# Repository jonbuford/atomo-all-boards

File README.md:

# atomo-all_boards
This is a collection of PCB designs for microcontroller development boards created for the Atomo line. We are releasing these files and designs to the world prior to our first production run. Any feedback on them is appreciated. 

Some basics:
1. We are releasing the raw design files and not the production silk screen with our commercial logo for Atomo. (We reserve the copyright on the Atomo brand.)
2. Yes, the refdes locations are on the parts for the most part. Earlier versions of the design attempted to keep all of the refdes markers in locations that could be used for silkscreen printing, but this required some very convoluted manual indications of what matches what. The density on these boards is just too high to have a clean 1:1 refdes printing on the boards. For the production silkscreens, we will be creating markings that is only for typical end use features and for major components or functional areas.
3. The 10-pin JTAG headers have been moved to the 26-pin/40-pin headers to reduce cost and to make all boards programmable using a Raspberry Pi or similar. 
4. Updated the 26-pin and 40-pin headers so that the pins are the same configuration for the first 26 pins. The 40-pin header is compatible with the ethernet adapter. 

So, this is the current state of the finished design files. To be added are the backplane and module files. The intent now is to try to move this into a more open development project to keep things growing. If you are interested in contributing, please contact the project.

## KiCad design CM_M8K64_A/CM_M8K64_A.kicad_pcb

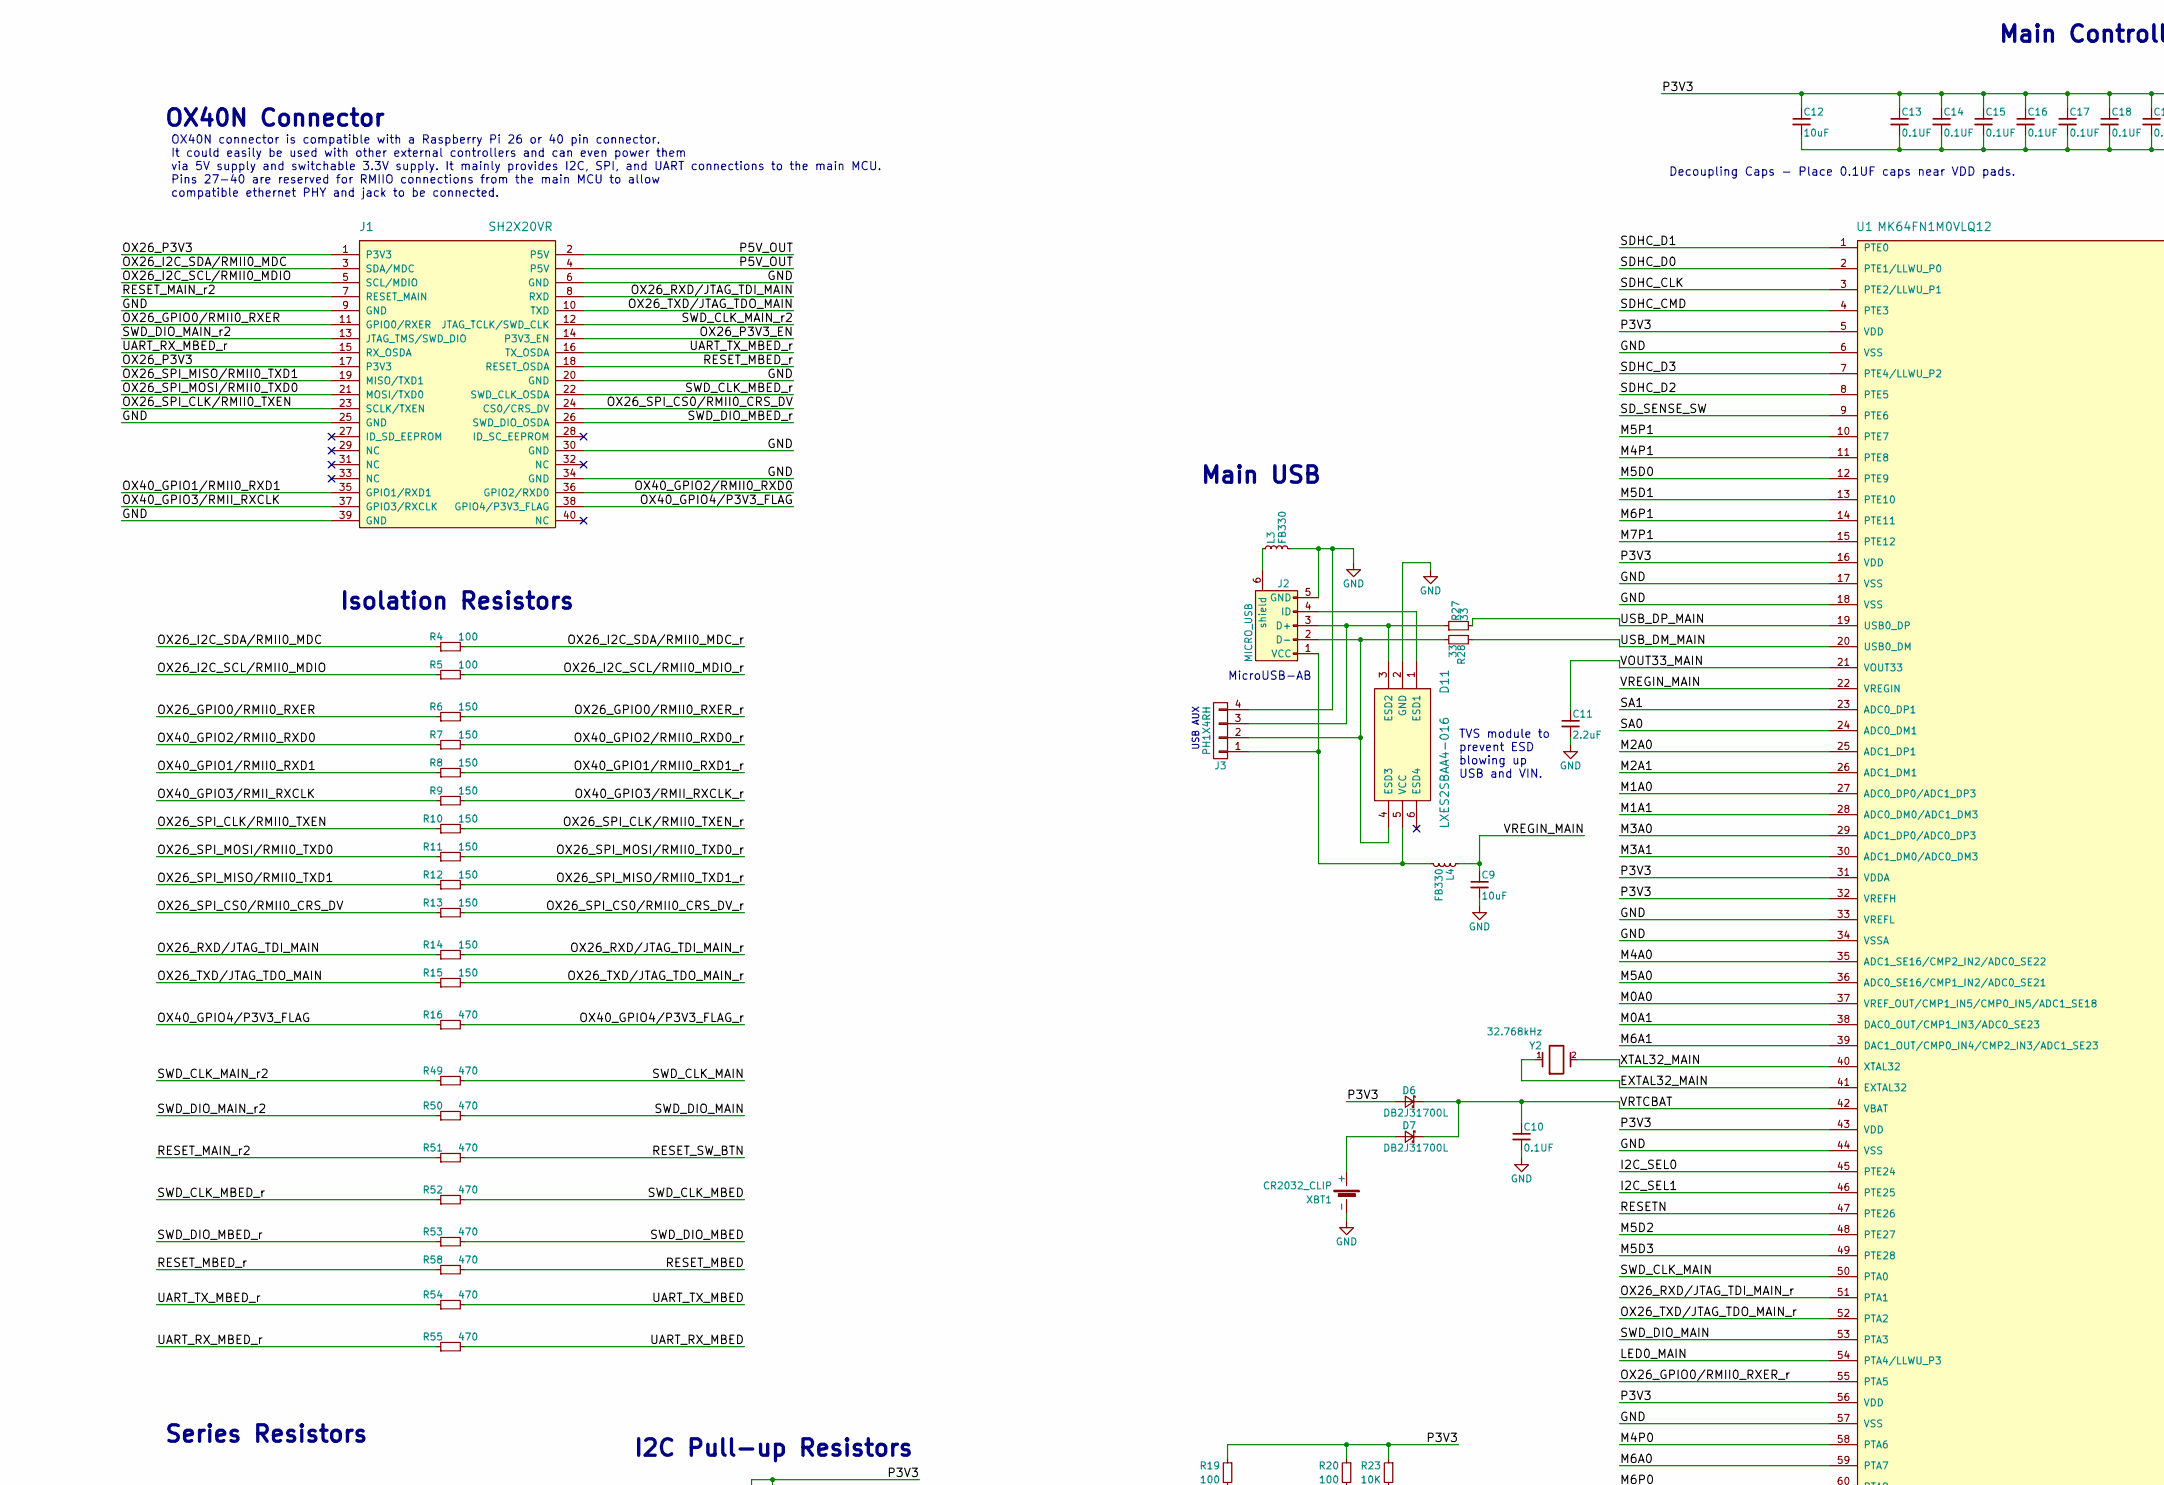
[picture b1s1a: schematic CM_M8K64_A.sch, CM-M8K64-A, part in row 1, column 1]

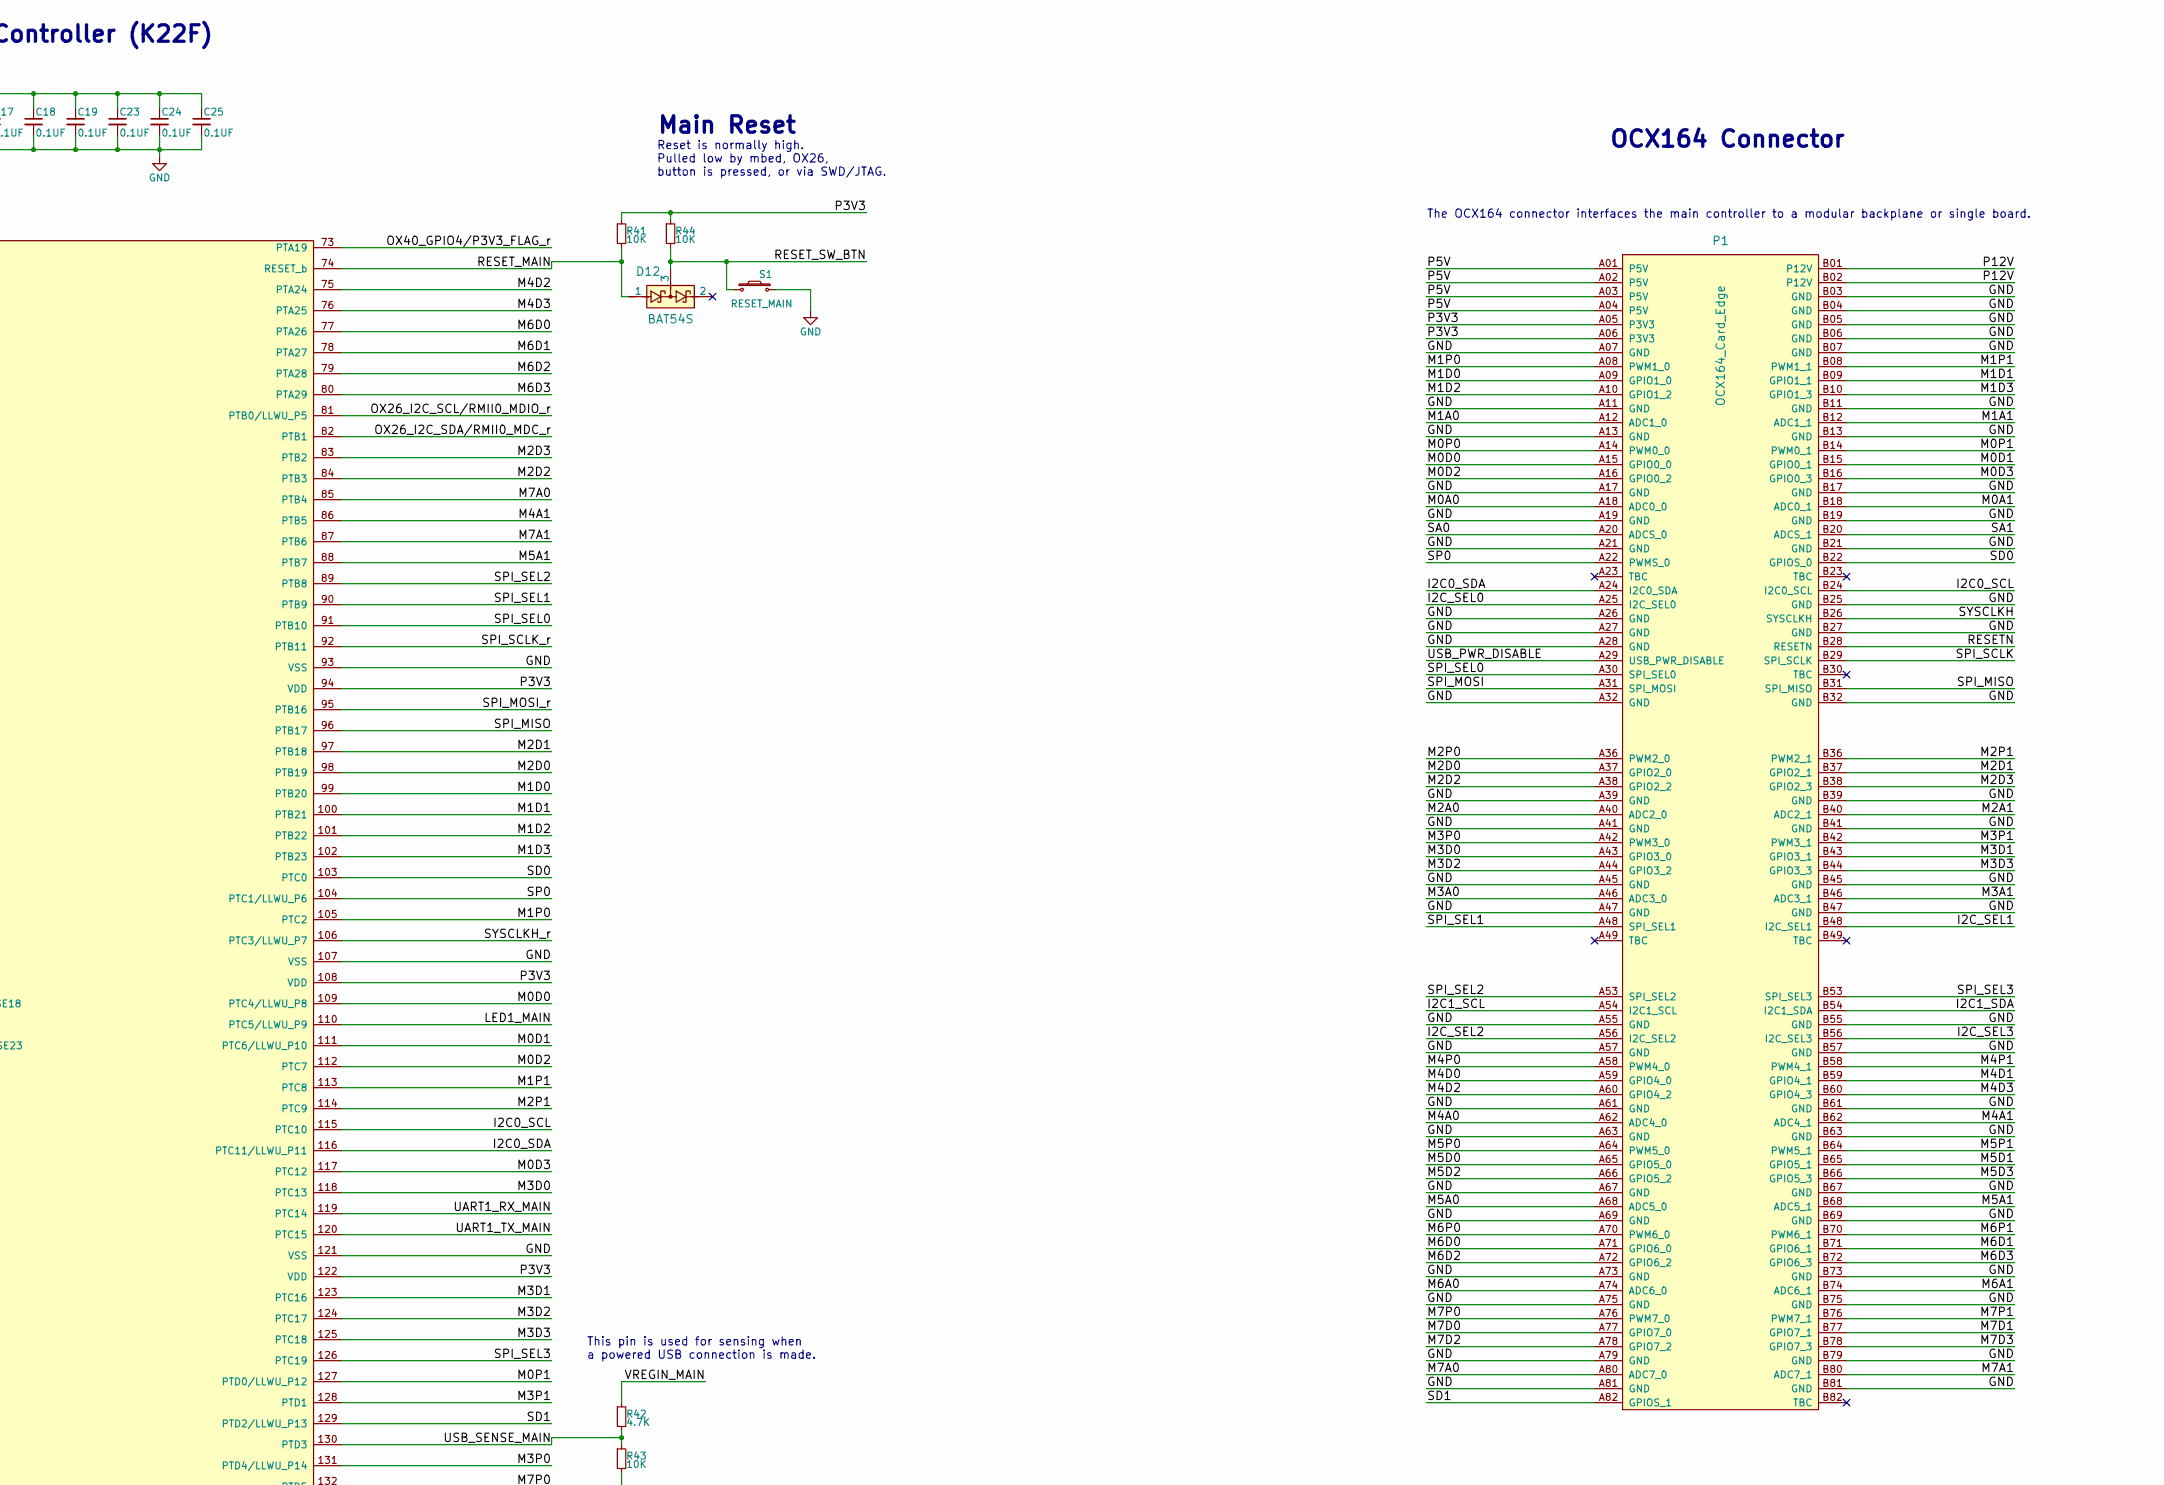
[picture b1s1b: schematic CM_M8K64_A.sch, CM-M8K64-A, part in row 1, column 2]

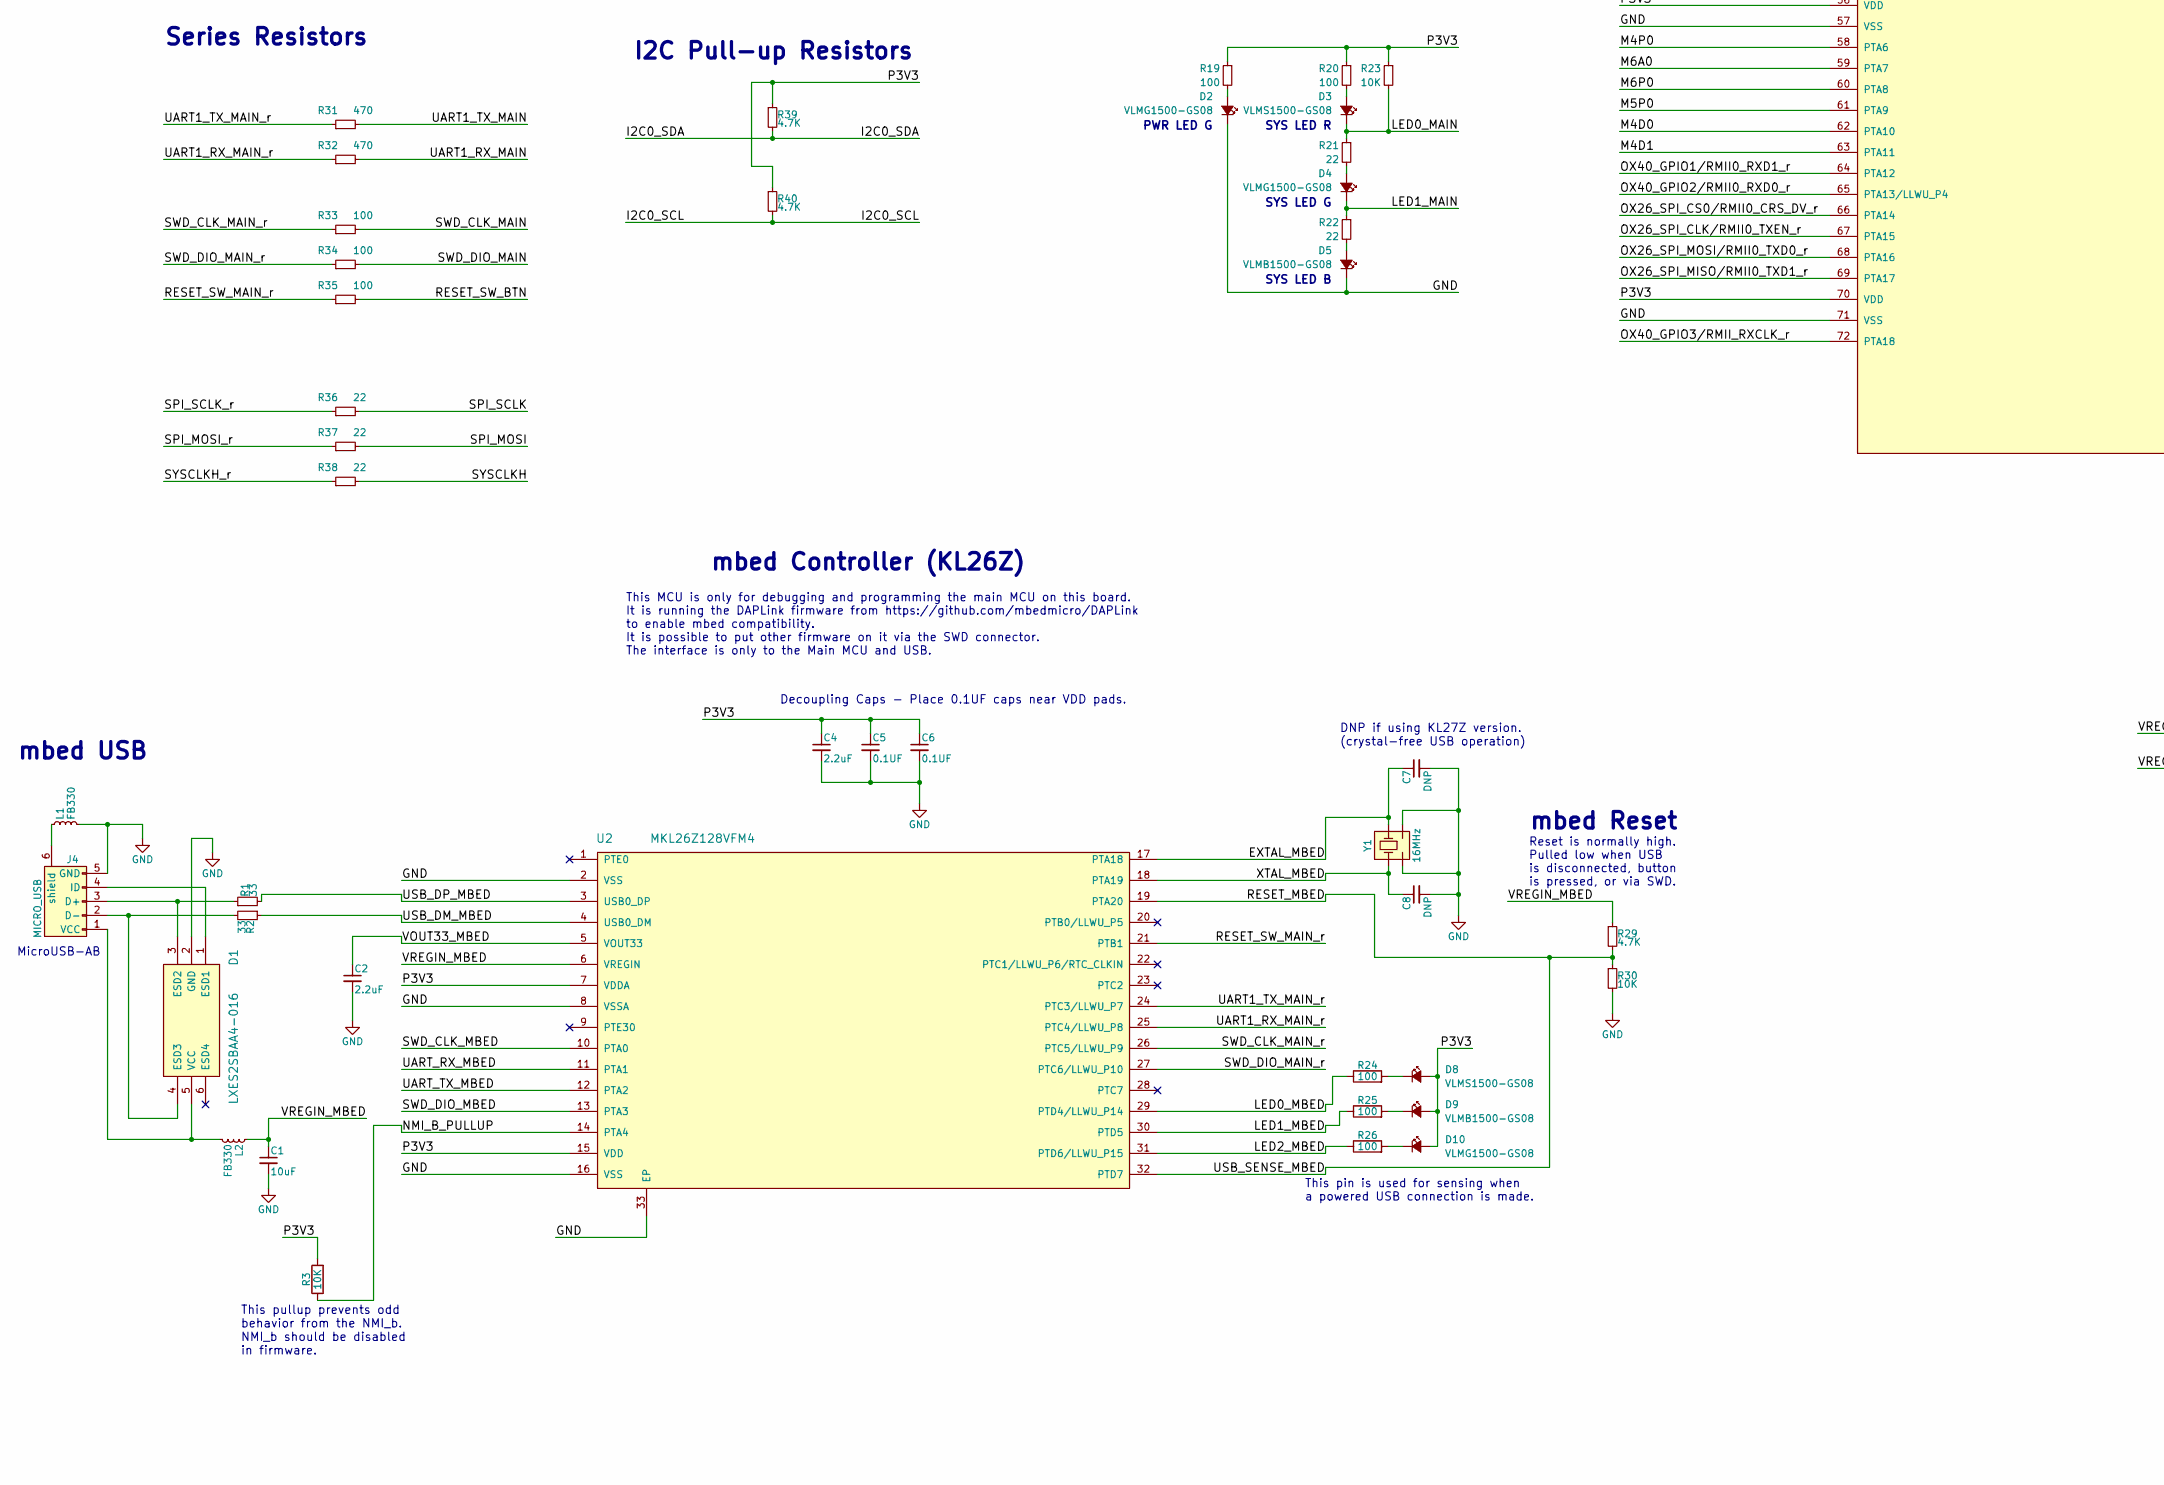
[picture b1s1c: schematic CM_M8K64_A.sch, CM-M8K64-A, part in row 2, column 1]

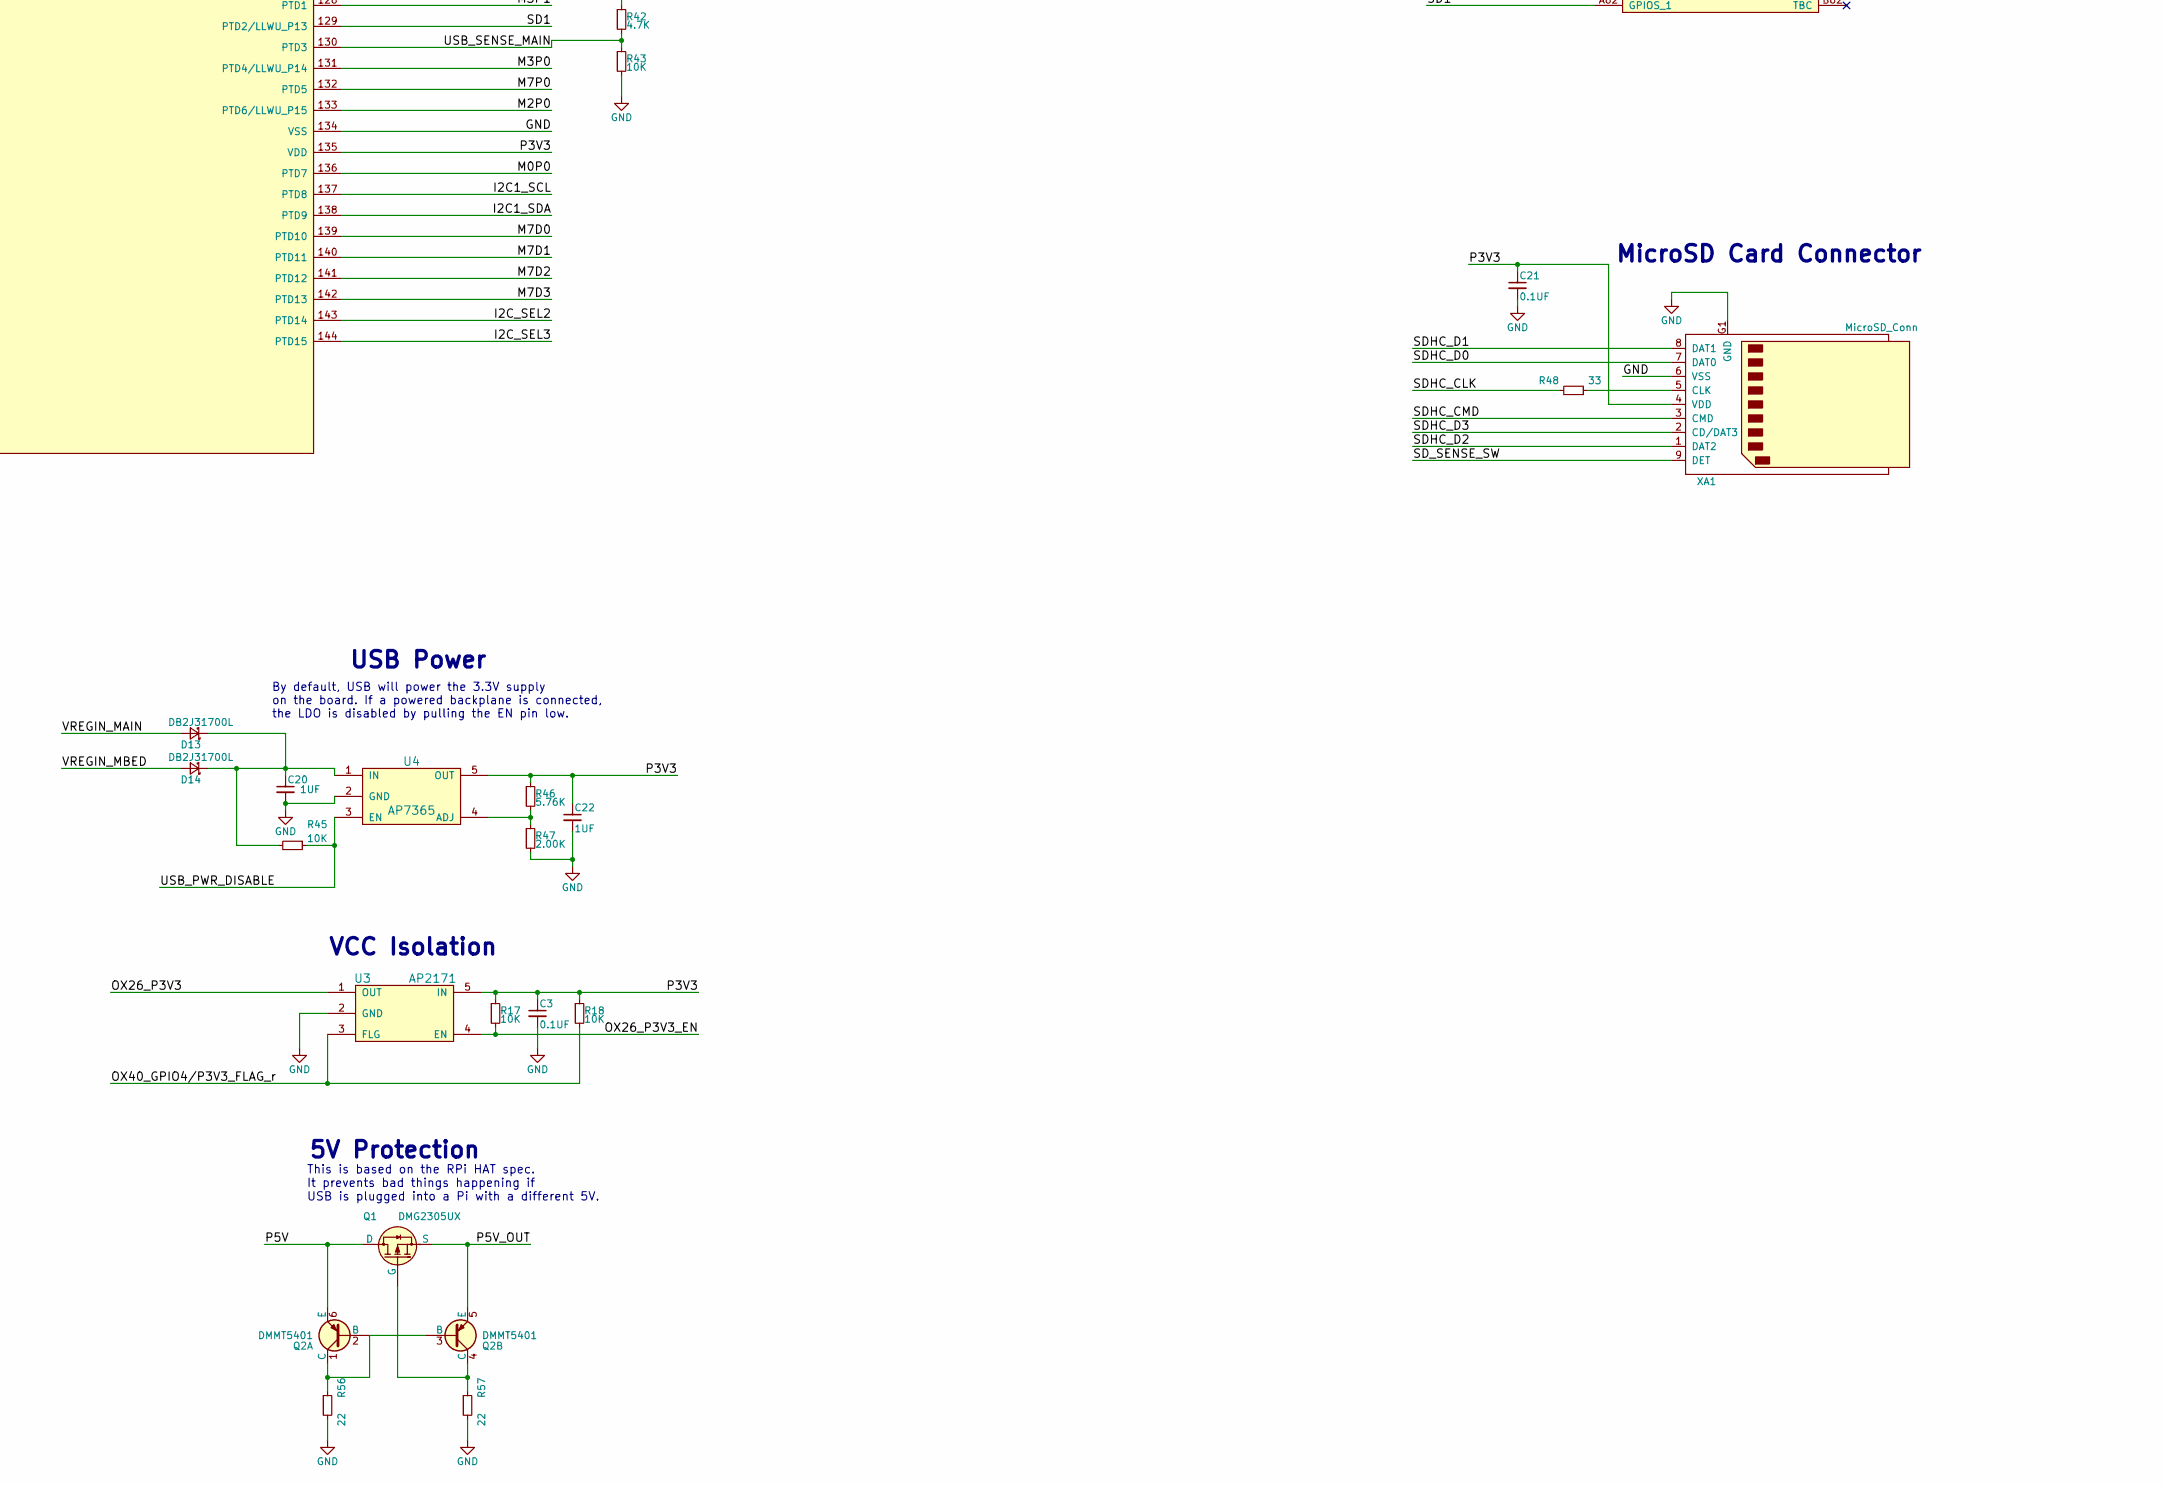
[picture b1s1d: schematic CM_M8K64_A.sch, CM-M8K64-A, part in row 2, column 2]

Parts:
C1, C9, C12: 10uF; C_0603; MPN GRM188R60J106KE47D
C2, C4, C11: 2.2uF; C_0402; MPN GRM155R60J225KE95D
C3, C5, C6, C10, C13, C14, C15, C16, C17, C18, C19, C21, C23, C24, C25: 0.1UF; C_0402; MPN GRM155R71H104ME14D
C7, C8: DNP; C_0402; MPN DNP
C20, C22: 1UF; C_0402; MPN GRM155R60J105KE19D
D1, D11: LXES2SBAA4-016; SOT-23-6; MPN LXES2SBAA4-016
D2, D4, D10: VLMG1500-GS08; LED_0402; MPN VLMG1500-GS08
D3, D8: VLMS1500-GS08; LED_0402; MPN VLMS1500-GS08
D5, D9: VLMB1500-GS08; LED_0402; MPN VLMB1500-GS08
D6, D7, D13, D14: DB2J31700L; SC-90A; MPN DB2J31700L
D12: BAT54S; SOT-23; MPN BAT54S,215
J1: SH2X20VR; OX40_W_PI_HOLE; MPN PPPC202LFBN-RC
J2, J4: MICRO_USB; Micro_USB_Molex_105017-0001; MPN 1050170001
J3: PH1X4RH; Pin_Header_Angled_1x04; MPN DNP
L1, L3: FB330; R_0603; MPN MPZ1608S331ATA00
L2, L4: FB330; R_0805; MPN MPZ2012S331AT000
P1: OCX164_Card_Edge; MPN DNP
Q1: DMG2305UX; SOT-23; MPN DMG2305UX-13
Q2: DMMT5401; SOT-23-6; MPN DMMT5401-7-F
R1, R2, R27, R28, R48: 33; R_0402; MPN RC0402JR-0733RL
R3, R17, R18, R23, R30, R41, R43, R44, R45: 10K; R_0402; MPN RC0402JR-0710KL
R4, R5, R19, R20, R24, R25, R26, R33, R34, R35: 100; R_0402; MPN RC0402JR-07100RL
R6, R7, R8, R9, R10, R11, R12, R13, R14, R15: 150; R_0402; MPN RC0402JR-07150RL
R16, R31, R32, R49, R50, R51, R52, R53, R54, R55, R58: 470; R_0402; MPN RC0402JR-07470RL
R21, R22, R36, R37, R38, R56, R57: 22; R_0402; MPN RC0402JR-0722RL
R29, R39, R40, R42: 4.7K; R_0402; MPN RC0402JR-074K7L
R46: 5.76K; R_0603; Tolerance 1%; MPN RC0603FR-075K76L
R47: 2.00K; R_0603; Tolerance 1%; MPN RC0603FR-072KL
S1: RESET_MAIN; Switch_TS-1101F_SZ_BEST; MPN TS-1101F
U1: MK64FN1M0VLQ12; LQFP-144_20x20mm_Pitch0.5mm; MPN MK64FN1M0VLQ12
U2: MKL26Z128VFM4; QFN32_w_TP_FS; MPN MKL26Z128VFM4
U3: AP2171; SOT-23-5; MPN AP2171WG-7
U4: AP7365; SOT-23-5; MPN AP7365-WG-7
XA1: MicroSD_Conn; 1051620101; MPN 1051620101
XBT1: CR2032_CLIP; KEYSTONE_3034; MPN 3034TR
Y1: 16MHz; XTAL3_2X2_5; MPN FA-238 16.0000MB-K3
Y2: 32.768kHz; XTAL_CYL_CAN_SMT; MPN G33270007

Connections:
/EXTAL32_MAIN: U1.41 (EXTAL32), Y2.1
/EXTAL_MBED: C7.1, U2.17 (PTA18), Y1.1
/I2C0_SCL: P1.B24 (I2C0_SCL), R40.2, U1.115 (PTC10)
/I2C0_SDA: P1.A24 (I2C0_SDA), R39.2, U1.116 (PTC11/LLWU_P11)
/I2C1_SCL: P1.A54 (I2C1_SCL), U1.137 (PTD8)
/I2C1_SDA: P1.B54 (I2C1_SDA), U1.138 (PTD9)
/I2C_SEL0: P1.A25 (I2C_SEL0), U1.45 (PTE24)
/I2C_SEL1: P1.B48 (I2C_SEL1), U1.46 (PTE25)
/I2C_SEL2: P1.A56 (I2C_SEL2), U1.143 (PTD14)
/I2C_SEL3: P1.B56 (I2C_SEL3), U1.144 (PTD15)
/LED0_MAIN: D3.1 (K), R21.1, R23.2, U1.54 (PTA4/LLWU_P3)
/LED0_MBED: R24.1, U2.29 (PTD4/LLWU_P14)
/LED1_MAIN: D4.1 (K), R22.1, U1.110 (PTC5/LLWU_P9)
/LED1_MBED: R25.1, U2.30 (PTD5)
/LED2_MBED: R26.1, U2.31 (PTD6/LLWU_P15)
/M0A0: P1.A18 (ADC0_0), U1.37 (VREF_OUT/CMP1_IN5/CMP0_IN5/ADC1_SE18)
/M0A1: P1.B18 (ADC0_1), U1.38 (DAC0_OUT/CMP1_IN3/ADC0_SE23)
/M0D0: P1.A15 (GPIO0_0), U1.109 (PTC4/LLWU_P8)
/M0D1: P1.B15 (GPIO0_1), U1.111 (PTC6/LLWU_P10)
/M0D2: P1.A16 (GPIO0_2), U1.112 (PTC7)
/M0D3: P1.B16 (GPIO0_3), U1.117 (PTC12)
/M0P0: P1.A14 (PWM0_0), U1.136 (PTD7)
/M0P1: P1.B14 (PWM0_1), U1.127 (PTD0/LLWU_P12)
/M1A0: P1.A12 (ADC1_0), U1.27 (ADC0_DP0/ADC1_DP3)
/M1A1: P1.B12 (ADC1_1), U1.28 (ADC0_DM0/ADC1_DM3)
/M1D0: P1.A09 (GPIO1_0), U1.99 (PTB20)
/M1D1: P1.B09 (GPIO1_1), U1.100 (PTB21)
/M1D2: P1.A10 (GPIO1_2), U1.101 (PTB22)
/M1D3: P1.B10 (GPIO1_3), U1.102 (PTB23)
/M1P0: P1.A08 (PWM1_0), U1.105 (PTC2)
/M1P1: P1.B08 (PWM1_1), U1.113 (PTC8)
/M2A0: P1.A40 (ADC2_0), U1.25 (ADC1_DP1)
/M2A1: P1.B40 (ADC2_1), U1.26 (ADC1_DM1)
/M2D0: P1.A37 (GPIO2_0), U1.98 (PTB19)
/M2D1: P1.B37 (GPIO2_1), U1.97 (PTB18)
/M2D2: P1.A38 (GPIO2_2), U1.84 (PTB3)
/M2D3: P1.B38 (GPIO2_3), U1.83 (PTB2)
/M2P0: P1.A36 (PWM2_0), U1.133 (PTD6/LLWU_P15)
/M2P1: P1.B36 (PWM2_1), U1.114 (PTC9)
/M3A0: P1.A46 (ADC3_0), U1.29 (ADC1_DP0/ADC0_DP3)
/M3A1: P1.B46 (ADC3_1), U1.30 (ADC1_DM0/ADC0_DM3)
/M3D0: P1.A43 (GPIO3_0), U1.118 (PTC13)
/M3D1: P1.B43 (GPIO3_1), U1.123 (PTC16)
/M3D2: P1.A44 (GPIO3_2), U1.124 (PTC17)
/M3D3: P1.B44 (GPIO3_3), U1.125 (PTC18)
/M3P0: P1.A42 (PWM3_0), U1.131 (PTD4/LLWU_P14)
/M3P1: P1.B42 (PWM3_1), U1.128 (PTD1)
/M4A0: P1.A62 (ADC4_0), U1.35 (ADC1_SE16/CMP2_IN2/ADC0_SE22)
/M4A1: P1.B62 (ADC4_1), U1.86 (PTB5)
/M4D0: P1.A59 (GPIO4_0), U1.62 (PTA10)
/M4D1: P1.B59 (GPIO4_1), U1.63 (PTA11)
/M4D2: P1.A60 (GPIO4_2), U1.75 (PTA24)
/M4D3: P1.B60 (GPIO4_3), U1.76 (PTA25)
/M4P0: P1.A58 (PWM4_0), U1.58 (PTA6)
/M4P1: P1.B58 (PWM4_1), U1.11 (PTE8)
/M5A0: P1.A68 (ADC5_0), U1.36 (ADC0_SE16/CMP1_IN2/ADC0_SE21)
/M5A1: P1.B68 (ADC5_1), U1.88 (PTB7)
/M5D0: P1.A65 (GPIO5_0), U1.12 (PTE9)
/M5D1: P1.B65 (GPIO5_1), U1.13 (PTE10)
/M5D2: P1.A66 (GPIO5_2), U1.48 (PTE27)
/M5D3: P1.B66 (GPIO5_3), U1.49 (PTE28)
/M5P0: P1.A64 (PWM5_0), U1.61 (PTA9)
/M5P1: P1.B64 (PWM5_1), U1.10 (PTE7)
/M6A0: P1.A74 (ADC6_0), U1.59 (PTA7)
/M6A1: P1.B74 (ADC6_1), U1.39 (DAC1_OUT/CMP0_IN4/CMP2_IN3/ADC1_SE23)
/M6D0: P1.A71 (GPIO6_0), U1.77 (PTA26)
/M6D1: P1.B71 (GPIO6_1), U1.78 (PTA27)
/M6D2: P1.A72 (GPIO6_2), U1.79 (PTA28)
/M6D3: P1.B72 (GPIO6_3), U1.80 (PTA29)
/M6P0: P1.A70 (PWM6_0), U1.60 (PTA8)
/M6P1: P1.B70 (PWM6_1), U1.14 (PTE11)
/M7A0: P1.A80 (ADC7_0), U1.85 (PTB4)
/M7A1: P1.B80 (ADC7_1), U1.87 (PTB6)
/M7D0: P1.A77 (GPIO7_0), U1.139 (PTD10)
/M7D1: P1.B77 (GPIO7_1), U1.140 (PTD11)
/M7D2: P1.A78 (GPIO7_2), U1.141 (PTD12)
/M7D3: P1.B78 (GPIO7_3), U1.142 (PTD13)
/M7P0: P1.A76 (PWM7_0), U1.132 (PTD5)
/M7P1: P1.B76 (PWM7_1), U1.15 (PTE12)
/NMI_B_PULLUP: R3.1, U2.14 (PTA4)
/OX26_GPIO0/RMII0_RXER: J1.11 (GPIO0/RXER), R6.1
/OX26_GPIO0/RMII0_RXER_r: R6.2, U1.55 (PTA5)
/OX26_I2C_SCL/RMII0_MDIO: J1.5 (SCL/MDIO), R5.1
/OX26_I2C_SCL/RMII0_MDIO_r: R5.2, U1.81 (PTB0/LLWU_P5)
/OX26_I2C_SDA/RMII0_MDC: J1.3 (SDA/MDC), R4.1
/OX26_I2C_SDA/RMII0_MDC_r: R4.2, U1.82 (PTB1)
/OX26_P3V3: J1.1 (P3V3), J1.17 (P3V3), U3.1 (OUT)
/OX26_P3V3_EN: J1.14 (P3V3_EN), R17.2, U3.4 (EN)
/OX26_RXD/JTAG_TDI_MAIN: J1.8 (RXD), R14.1
/OX26_RXD/JTAG_TDI_MAIN_r: R14.2, U1.51 (PTA1)
/OX26_SPI_CLK/RMII0_TXEN: J1.23 (SCLK/TXEN), R10.1
/OX26_SPI_CLK/RMII0_TXEN_r: R10.2, U1.67 (PTA15)
/OX26_SPI_CS0/RMII0_CRS_DV: J1.24 (CS0/CRS_DV), R13.1
/OX26_SPI_CS0/RMII0_CRS_DV_r: R13.2, U1.66 (PTA14)
/OX26_SPI_MISO/RMII0_TXD1: J1.19 (MISO/TXD1), R12.1
/OX26_SPI_MISO/RMII0_TXD1_r: R12.2, U1.69 (PTA17)
/OX26_SPI_MOSI/RMII0_TXD0: J1.21 (MOSI/TXD0), R11.1
/OX26_SPI_MOSI/RMII0_TXD0_r: R11.2, U1.68 (PTA16)
/OX26_TXD/JTAG_TDO_MAIN: J1.10 (TXD), R15.1
/OX26_TXD/JTAG_TDO_MAIN_r: R15.2, U1.52 (PTA2)
/OX40_GPIO1/RMII0_RXD1: J1.35 (GPIO1/RXD1), R8.1
/OX40_GPIO1/RMII0_RXD1_r: R8.2, U1.64 (PTA12)
/OX40_GPIO2/RMII0_RXD0: J1.36 (GPIO2/RXD0), R7.1
/OX40_GPIO2/RMII0_RXD0_r: R7.2, U1.65 (PTA13/LLWU_P4)
/OX40_GPIO3/RMII_RXCLK: J1.37 (GPIO3/RXCLK), R9.1
/OX40_GPIO3/RMII_RXCLK_r: R9.2, U1.72 (PTA18)
/OX40_GPIO4/P3V3_FLAG: J1.38 (GPIO4/P3V3_FLAG), R16.1
/OX40_GPIO4/P3V3_FLAG_r: R16.2, R18.2, U1.73 (PTA19), U3.3 (FLG)
/P3V3: C3.1, C4.1, C5.1, C6.1, C12.1, C13.1, C14.1, C15.1, C16.1, C17.1, C18.1, C19.1, C21.1, C22.1, C23.1, C24.1, C25.1, D6.2 (A), D8.2 (A), D9.2 (A), D10.2 (A), P1.A05 (P3V3), P1.A06 (P3V3), R3.2, R17.1, R18.1, R19.1, R20.1, R23.1, R39.1, R40.1, R41.1, R44.1, R46.1, U1.5 (VDD), U1.16 (VDD), U1.31 (VDDA), U1.32 (VREFH), U1.43 (VDD), U1.56 (VDD), U1.70 (VDD), U1.94 (VDD), U1.108 (VDD), U1.122 (VDD), U1.135 (VDD), U2.7 (VDDA), U2.15 (VDD), U3.5 (IN), U4.5 (OUT), XA1.4 (VDD)
/P5V: P1.A01 (P5V), P1.A02 (P5V), P1.A03 (P5V), P1.A04 (P5V), Q1.3 (D), Q2.6 (E)
/P5V_OUT: J1.2 (P5V), J1.4 (P5V), Q1.2 (S), Q2.5 (E)
/P12V: P1.B01 (P12V), P1.B02 (P12V)
/RESETN: P1.B28 (RESETN), U1.47 (PTE26)
/RESET_MAIN: D12.1, R41.2, U1.74 (RESET_b)
/RESET_MAIN_r2: J1.7 (RESET_MAIN), R51.1
/RESET_MBED: R29.2, R30.1, R58.2, U2.19 (PTA20), U2.32 (PTD7)
/RESET_MBED_r: J1.18 (RESET_OSDA), R58.1
/RESET_SW_BTN: D12.3, R35.2, R44.2, R51.2, S1.1
/RESET_SW_MAIN_r: R35.1, U2.21 (PTB1)
/SA0: P1.A20 (ADCS_0), U1.24 (ADC0_DM1)
/SA1: P1.B20 (ADCS_1), U1.23 (ADC0_DP1)
/SD0: P1.B22 (GPIOS_0), U1.103 (PTC0)
/SD1: P1.A82 (GPIOS_1), U1.129 (PTD2/LLWU_P13)
/SDHC_CLK: R48.2, U1.3 (PTE2/LLWU_P1)
/SDHC_CMD: U1.4 (PTE3), XA1.3 (CMD)
/SDHC_D0: U1.2 (PTE1/LLWU_P0), XA1.7 (DAT0)
/SDHC_D1: U1.1 (PTE0), XA1.8 (DAT1)
/SDHC_D2: U1.8 (PTE5), XA1.1 (DAT2)
/SDHC_D3: U1.7 (PTE4/LLWU_P2), XA1.2 (CD/DAT3)
/SD_SENSE_SW: U1.9 (PTE6), XA1.9 (DET)
/SP0: P1.A22 (PWMS_0), U1.104 (PTC1/LLWU_P6)
/SPI_MISO: P1.B31 (SPI_MISO), U1.96 (PTB17)
/SPI_MOSI: P1.A31 (SPI_MOSI), R37.2
/SPI_MOSI_r: R37.1, U1.95 (PTB16)
/SPI_SCLK: P1.B29 (SPI_SCLK), R36.2
/SPI_SCLK_r: R36.1, U1.92 (PTB11)
/SPI_SEL0: P1.A30 (SPI_SEL0), U1.91 (PTB10)
/SPI_SEL1: P1.A48 (SPI_SEL1), U1.90 (PTB9)
/SPI_SEL2: P1.A53 (SPI_SEL2), U1.89 (PTB8)
/SPI_SEL3: P1.B53 (SPI_SEL3), U1.126 (PTC19)
/SWD_CLK_MAIN: R33.2, R49.2, U1.50 (PTA0)
/SWD_CLK_MAIN_r: R33.1, U2.26 (PTC5/LLWU_P9)
/SWD_CLK_MAIN_r2: J1.12 (JTAG_TCLK/SWD_CLK), R49.1
/SWD_CLK_MBED: R52.2, U2.10 (PTA0)
/SWD_CLK_MBED_r: J1.22 (SWD_CLK_OSDA), R52.1
/SWD_DIO_MAIN: R34.2, R50.2, U1.53 (PTA3)
/SWD_DIO_MAIN_r: R34.1, U2.27 (PTC6/LLWU_P10)
/SWD_DIO_MAIN_r2: J1.13 (JTAG_TMS/SWD_DIO), R50.1
/SWD_DIO_MBED: R53.2, U2.13 (PTA3)
/SWD_DIO_MBED_r: J1.26 (SWD_DIO_OSDA), R53.1
/SYSCLKH: P1.B26 (SYSCLKH), R38.2
/SYSCLKH_r: R38.1, U1.106 (PTC3/LLWU_P7)
/UART1_RX_MAIN: R32.2, U1.119 (PTC14)
/UART1_RX_MAIN_r: R32.1, U2.25 (PTC4/LLWU_P8)
/UART1_TX_MAIN: R31.2, U1.120 (PTC15)
/UART1_TX_MAIN_r: R31.1, U2.24 (PTC3/LLWU_P7)
/UART_RX_MBED: R55.2, U2.11 (PTA1)
/UART_RX_MBED_r: J1.15 (RX_OSDA), R55.1
/UART_TX_MBED: R54.2, U2.12 (PTA2)
/UART_TX_MBED_r: J1.16 (TX_OSDA), R54.1
/USB_DM_MAIN: R28.1, U1.20 (USB0_DM)
/USB_DM_MBED: R2.1, U2.4 (USB0_DM)
/USB_DP_MAIN: R27.2, U1.19 (USB0_DP)
/USB_DP_MBED: R1.2, U2.3 (USB0_DP)
/USB_PWR_DISABLE: P1.A29 (USB_PWR_DISABLE), R45.1, U4.3 (EN)
/USB_SENSE_MAIN: R42.2, R43.1, U1.130 (PTD3)
/VOUT33_MAIN: C11.1, U1.21 (VOUT33)
/VOUT33_MBED: C2.1, U2.5 (VOUT33)
/VREGIN_MAIN: C9.1, D13.2 (A), L4.1, R42.1, U1.22 (VREGIN)
/VREGIN_MBED: C1.1, D14.2 (A), L2.1, R29.1, U2.6 (VREGIN)
/VRTCBAT: C10.1, D6.1 (K), D7.1 (K), U1.42 (VBAT)
/XTAL32_MAIN: U1.40 (XTAL32), Y2.2
/XTAL_MBED: C8.1, U2.18 (PTA19), Y1.3
GND: C1.2, C2.2, C3.2, C4.2, C5.2, C6.2, C7.2, C8.2, C9.2, C10.2, C11.2, C12.2, C13.2, C14.2, C15.2, C16.2, C17.2, C18.2, C19.2, C20.2, C21.2, C22.2, C23.2, C24.2, C25.2, D1.2 (GND), D2.1 (K), D5.1 (K), D11.2 (GND), J1.6 (GND), J1.9 (GND), J1.20 (GND), J1.25 (GND), J1.30 (GND), J1.34 (GND), J1.39 (GND), J2.5 (GND), J3.4, J4.5 (GND), L1.2, L3.2, P1.A07 (GND), P1.A11 (GND), P1.A13 (GND), P1.A17 (GND), P1.A19 (GND), P1.A21 (GND), P1.A26 (GND), P1.A27 (GND), P1.A28 (GND), P1.A32 (GND), P1.A39 (GND), P1.A41 (GND), P1.A45 (GND), P1.A47 (GND), P1.A55 (GND), P1.A57 (GND), P1.A61 (GND), P1.A63 (GND), P1.A67 (GND), P1.A69 (GND), P1.A73 (GND), P1.A75 (GND), P1.A79 (GND), P1.A81 (GND), P1.B03 (GND), P1.B04 (GND), P1.B05 (GND), P1.B06 (GND), P1.B07 (GND), P1.B11 (GND), P1.B13 (GND), P1.B17 (GND), P1.B19 (GND), P1.B21 (GND), P1.B25 (GND), P1.B27 (GND), P1.B32 (GND), P1.B39 (GND), P1.B41 (GND), P1.B45 (GND), P1.B47 (GND), P1.B55 (GND), P1.B57 (GND), P1.B61 (GND), P1.B63 (GND), P1.B67 (GND), P1.B69 (GND), P1.B73 (GND), P1.B75 (GND), P1.B79 (GND), P1.B81 (GND), R30.2, R43.2, R47.2, R56.2, R57.2, S1.2, U1.6 (VSS), U1.17 (VSS), U1.18 (VSS), U1.33 (VREFL), U1.34 (VSSA), U1.44 (VSS), U1.57 (VSS), U1.71 (VSS), U1.93 (VSS), U1.107 (VSS), U1.121 (VSS), U1.134 (VSS), U2.2 (VSS), U2.8 (VSSA), U2.16 (VSS), U2.33 (EP), U3.2 (GND), U4.2 (GND), XA1.6 (VSS), XA1.G1 (GND), XA1.G2 (GND), XA1.G3 (GND), XA1.G4 (GND), XBT1.1 (-), Y1.2 (GND), Y1.4 (GND)
unnamed: C20.1, D13.1 (K), D14.1 (K), R45.2, U4.1 (IN)
unnamed: D1.1 (ESD1), J4.4 (ID)
unnamed: D1.3 (ESD2), J4.3 (D+), R1.1
unnamed: D1.4 (ESD3), J4.2 (D-), R2.2
unnamed: D1.5 (VCC), J4.1 (VCC), L2.2
unnamed: D2.2 (A), R19.2
unnamed: D3.2 (A), R20.2
unnamed: D4.2 (A), R21.2
unnamed: D5.2 (A), R22.2
unnamed: D7.2 (A), XBT1.2 (+)
unnamed: D8.1 (K), R24.2
unnamed: D9.1 (K), R25.2
unnamed: D10.1 (K), R26.2
unnamed: D11.1 (ESD1), J2.4 (ID)
unnamed: D11.3 (ESD2), J2.3 (D+), J3.3, R27.1
unnamed: D11.4 (ESD3), J2.2 (D-), J3.2, R28.2
unnamed: D11.5 (VCC), J2.1 (VCC), J3.1, L4.2
unnamed: J2.6 (shield), L3.1
unnamed: J4.6 (shield), L1.1
unnamed: Q1.1 (G), Q2.4 (C), R57.1
unnamed: Q2.1 (C), Q2.2 (B), Q2.3 (B), R56.1
unnamed: R46.2, R47.1, U4.4 (ADJ)
unnamed: R48.1, XA1.5 (CLK)

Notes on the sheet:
Decoupling Caps - Place 0.1UF caps near VDD pads.
OX40N Connector
mbed Controller (KL26Z)
Main Controller (K22F)
OCX164 Connector
This pin is used for sensing when a powered USB connection is made.
TVS module to prevent ESD blowing up USB and VIN.
MicroUSB-AB
MicroSD Card Connector
Main USB
mbed USB
Main Reset
mbed Reset
Reset is normally high. Pulled low when USB is disconnected, button is pressed, or via SWD.
Reset is normally high. Pulled low by mbed, OX26, button is pressed, or via SWD/JTAG.
SYS LED B
SYS LED R
SYS LED G
OX40N connector is compatible with a Raspberry Pi 26 or 40 pin connector. It could easily be used with other external controllers and can even power them via 5V supply and switchable 3.3V supply. It mainly provides I2C, SPI, and UART connections to the main MCU. Pins 27-40 are reserved for RMIIO co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
The OCX164 connector interfaces the main controller to a modular backplane or single board.
This MCU is only for debugging and programming the main MCU on this board. It is running the DAPLink firmware from https://github.com/mbedmicro/DAPLink to enable mbed compatibility. It is possible to put other firmware on it via the SWD connector. The interface is only to the Main MCU and USB.
This pullup prevents odd behavior from the NMI_b. NMI_b should be disabled in firmware.
USB Power
By default, USB will power the 3.3V supply on the board. If a powered backplane is connected, the LDO is disabled by pulling the EN pin low.
Series Resistors
I2C Pull-up Resistors
DNP if using KL27Z version. (crystal-free USB operation)
Isolation Resistors
VCC Isolation
PWR LED G
USB AUX
5V Protection
This is based on the RPi HAT spec. It prevents bad things happening if USB is plugged into a Pi with a different 5V.

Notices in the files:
parts and their libraries:
Copyright 2016 Accelerated Designs. All rights reserved.
